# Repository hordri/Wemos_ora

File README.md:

# Wemos_ora
Nixie clock with Wemos d1 mini and integrated switchmode supply

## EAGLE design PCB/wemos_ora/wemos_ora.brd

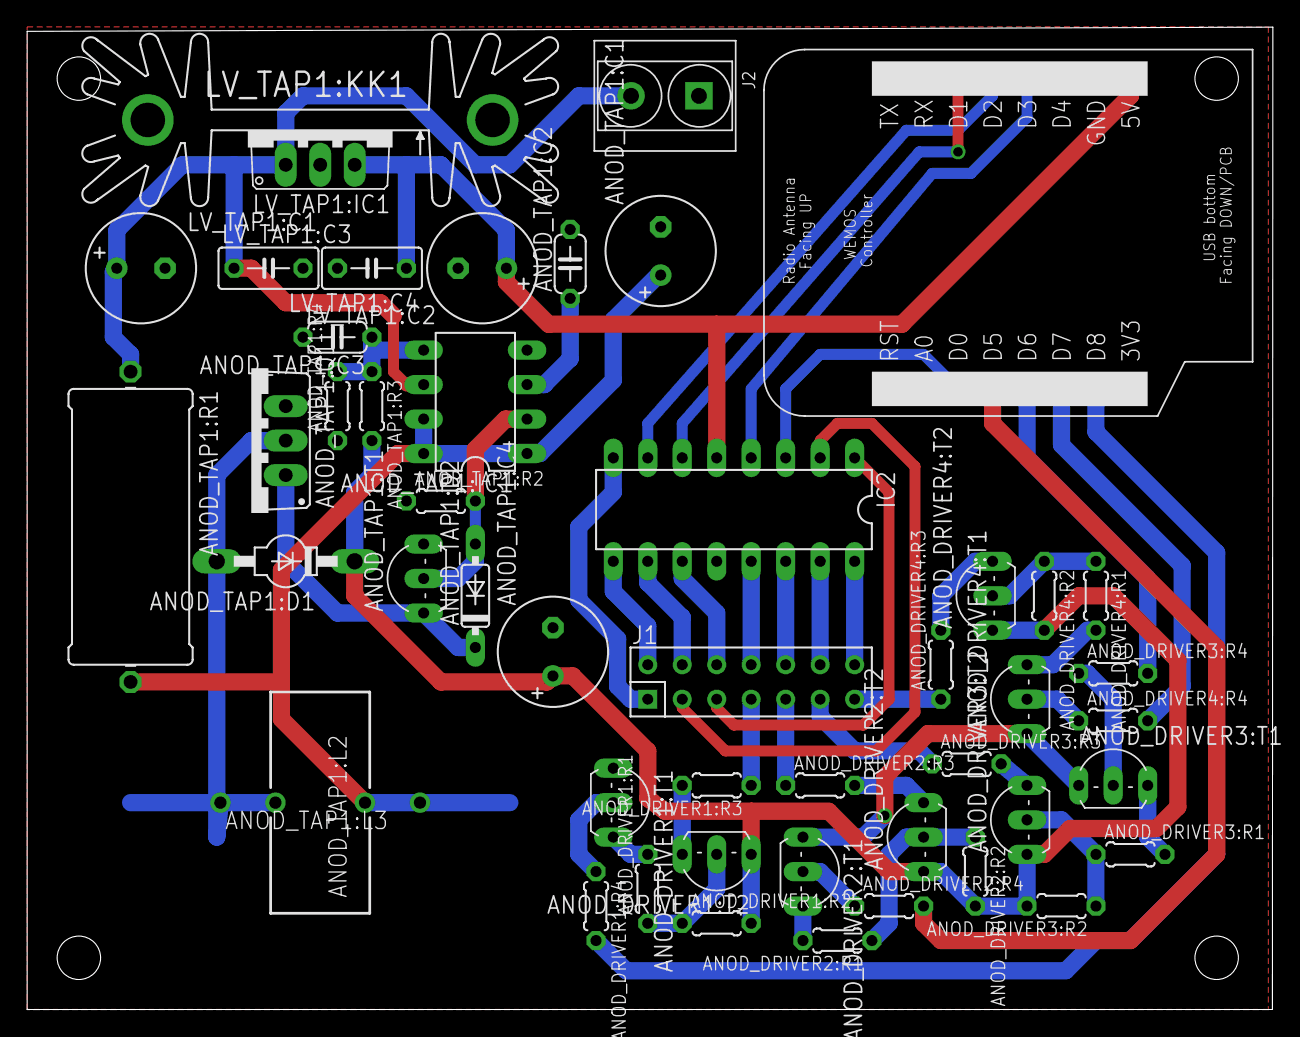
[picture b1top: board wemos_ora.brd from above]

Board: 2 copper layers, 91.8 x 72.4 mm, 50 parts (1 on the bottom side), 48 nets.

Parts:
ANOD_DRIVER1:R1, ANOD_DRIVER2:R1, ANOD_DRIVER3:R1, ANOD_DRIVER4:R1: 470k; 0204/5
ANOD_DRIVER1:R2, ANOD_DRIVER2:R2, ANOD_DRIVER3:R2, ANOD_DRIVER4:R2: 100k; 0204/5
ANOD_DRIVER1:R3, ANOD_DRIVER2:R3, ANOD_DRIVER3:R3, ANOD_DRIVER4:R3: 15k; 0204/5
ANOD_DRIVER1:R4, ANOD_DRIVER2:R4, ANOD_DRIVER3:R4, ANOD_DRIVER4:R4: 22k; 0204/5
ANOD_DRIVER1:T1, ANOD_DRIVER2:T1, ANOD_DRIVER3:T1, ANOD_DRIVER4:T1: MPSA42; TO92-EBC
ANOD_DRIVER1:T2, ANOD_DRIVER2:T2, ANOD_DRIVER3:T2, ANOD_DRIVER4:T2: MPSA92; TO92-EBC
ANOD_TAP1:C1: 220u; E3,5-8
ANOD_TAP1:C2: 2n2; C050-024X044
ANOD_TAP1:C3: 10n; C050-024X044
ANOD_TAP1:C4: 2u2; E3,5-8
ANOD_TAP1:D1: BYV27; SOD57-10
ANOD_TAP1:D2: 1N4148DO35-7; DO35-7
ANOD_TAP1:IC1: MC34063AP; DIL08
ANOD_TAP1:L1: PM2120
ANOD_TAP1:L2: TJ3-U1
ANOD_TAP1:L3: TJ3-U2
ANOD_TAP1:Q1: IRF740; TO220BV
ANOD_TAP1:R1: 0R47; 0922/22
ANOD_TAP1:R2: 1k; 0204/5
ANOD_TAP1:R3: 470k; 0204/5
ANOD_TAP1:R4: 3k3; 0204/5
ANOD_TAP1:T1: MPSA92; TO92-EBC
IC2: 74141N; DIL16
J1: CON_HEADER_2X07-PTH; M2X7
J2: 2p-5.08; H2-5.0-10.5X8.0MM
LV_TAP1:C1, LV_TAP1:C2: 470u; E3,5-8
LV_TAP1:C3, LV_TAP1:C4: 100n; C050-030X075
LV_TAP1:IC1: 7805TV; TO220V
LV_TAP1:KK1: SK104-PAD
U$1: WEMOS

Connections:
+5V: IC2.5, LV_TAP1:C2.+, LV_TAP1:C4.1, LV_TAP1:IC1.3, U$1.5V
+9V: ANOD_TAP1:IC1.6, ANOD_TAP1:R1.1, J2.2, LV_TAP1:C1.+, LV_TAP1:C3.1, LV_TAP1:IC1.1
+24V: ANOD_DRIVER1:R2.2, ANOD_DRIVER1:T2.E, ANOD_DRIVER2:R2.2, ANOD_DRIVER2:T2.E, ANOD_DRIVER3:R2.2, ANOD_DRIVER3:T2.E, ANOD_DRIVER4:R2.2, ANOD_DRIVER4:T2.E, ANOD_TAP1:C4.+, ANOD_TAP1:D1.C, ANOD_TAP1:R3.2
ANOD_DRIVER1:N$1: ANOD_DRIVER1:R3.2, ANOD_DRIVER1:T2.C
ANOD_DRIVER1:N$2: ANOD_DRIVER1:R1.1, ANOD_DRIVER1:R2.1, ANOD_DRIVER1:T2.B
ANOD_DRIVER1:N$3: ANOD_DRIVER1:R1.2, ANOD_DRIVER1:T1.C
ANOD_DRIVER1:N$4: ANOD_DRIVER1:R4.1, ANOD_DRIVER1:T1.B
ANOD_DRIVER2:N$1: ANOD_DRIVER2:R3.2, ANOD_DRIVER2:T2.C
ANOD_DRIVER2:N$2: ANOD_DRIVER2:R1.1, ANOD_DRIVER2:R2.1, ANOD_DRIVER2:T2.B
ANOD_DRIVER2:N$3: ANOD_DRIVER2:R1.2, ANOD_DRIVER2:T1.C
ANOD_DRIVER2:N$4: ANOD_DRIVER2:R4.1, ANOD_DRIVER2:T1.B
ANOD_DRIVER3:N$1: ANOD_DRIVER3:R3.2, ANOD_DRIVER3:T2.C
ANOD_DRIVER3:N$2: ANOD_DRIVER3:R1.1, ANOD_DRIVER3:R2.1, ANOD_DRIVER3:T2.B
ANOD_DRIVER3:N$3: ANOD_DRIVER3:R1.2, ANOD_DRIVER3:T1.C
ANOD_DRIVER3:N$4: ANOD_DRIVER3:R4.1, ANOD_DRIVER3:T1.B
ANOD_DRIVER4:N$1: ANOD_DRIVER4:R3.2, ANOD_DRIVER4:T2.C
ANOD_DRIVER4:N$2: ANOD_DRIVER4:R1.1, ANOD_DRIVER4:R2.1, ANOD_DRIVER4:T2.B
ANOD_DRIVER4:N$3: ANOD_DRIVER4:R1.2, ANOD_DRIVER4:T1.C
ANOD_DRIVER4:N$4: ANOD_DRIVER4:R4.1, ANOD_DRIVER4:T1.B
ANOD_TAP1:N$1: ANOD_TAP1:C1.+, ANOD_TAP1:IC1.1, ANOD_TAP1:IC1.7, ANOD_TAP1:IC1.8, ANOD_TAP1:L1.1, ANOD_TAP1:L2.1, ANOD_TAP1:L3.1, ANOD_TAP1:R1.2
ANOD_TAP1:N$3: ANOD_TAP1:D1.A, ANOD_TAP1:L1.2, ANOD_TAP1:L2.2, ANOD_TAP1:L3.2, ANOD_TAP1:Q1.D
ANOD_TAP1:N$4: ANOD_TAP1:D2.A, ANOD_TAP1:IC1.2, ANOD_TAP1:R2.2, ANOD_TAP1:T1.B
ANOD_TAP1:N$5: ANOD_TAP1:D2.C, ANOD_TAP1:Q1.G, ANOD_TAP1:T1.E
ANOD_TAP1:N$8: ANOD_TAP1:C2.1, ANOD_TAP1:IC1.3
ANOD_TAP1:N$14: ANOD_TAP1:C3.1, ANOD_TAP1:IC1.5, ANOD_TAP1:R3.1, ANOD_TAP1:R4.2
GND: ANOD_DRIVER1:T1.E, ANOD_DRIVER2:T1.E, ANOD_DRIVER3:T1.E, ANOD_DRIVER4:T1.E, ANOD_TAP1:C1.-, ANOD_TAP1:C2.2, ANOD_TAP1:C3.2, ANOD_TAP1:C4.-, ANOD_TAP1:IC1.4, ANOD_TAP1:Q1.S, ANOD_TAP1:R2.1, ANOD_TAP1:R4.1, ANOD_TAP1:T1.C, IC2.12, J2.1, LV_TAP1:C1.-, LV_TAP1:C2.-, LV_TAP1:C3.2, LV_TAP1:C4.2, LV_TAP1:IC1.2, U$1.GND
unnamed: IC2.16, J1.14
unnamed: IC2.15, J1.12
unnamed: IC2.8, J1.1
unnamed: IC2.9, J1.2
unnamed: IC2.13, J1.8
unnamed: IC2.14, J1.10
unnamed: IC2.11, J1.6
unnamed: IC2.10, J1.4
unnamed: IC2.1, J1.5
unnamed: IC2.2, J1.3
unnamed: ANOD_DRIVER1:R3.1, J1.7
unnamed: ANOD_DRIVER2:R3.1, J1.9
unnamed: ANOD_DRIVER3:R3.1, J1.11
unnamed: ANOD_DRIVER4:R3.1, J1.13
unnamed: IC2.3, U$1.D0
unnamed: IC2.6, U$1.D1
unnamed: IC2.7, U$1.D2
unnamed: IC2.4, U$1.D3
unnamed: ANOD_DRIVER1:R4.2, U$1.D8
unnamed: ANOD_DRIVER2:R4.2, U$1.D5
unnamed: ANOD_DRIVER3:R4.2, U$1.D6
unnamed: ANOD_DRIVER4:R4.2, U$1.D7

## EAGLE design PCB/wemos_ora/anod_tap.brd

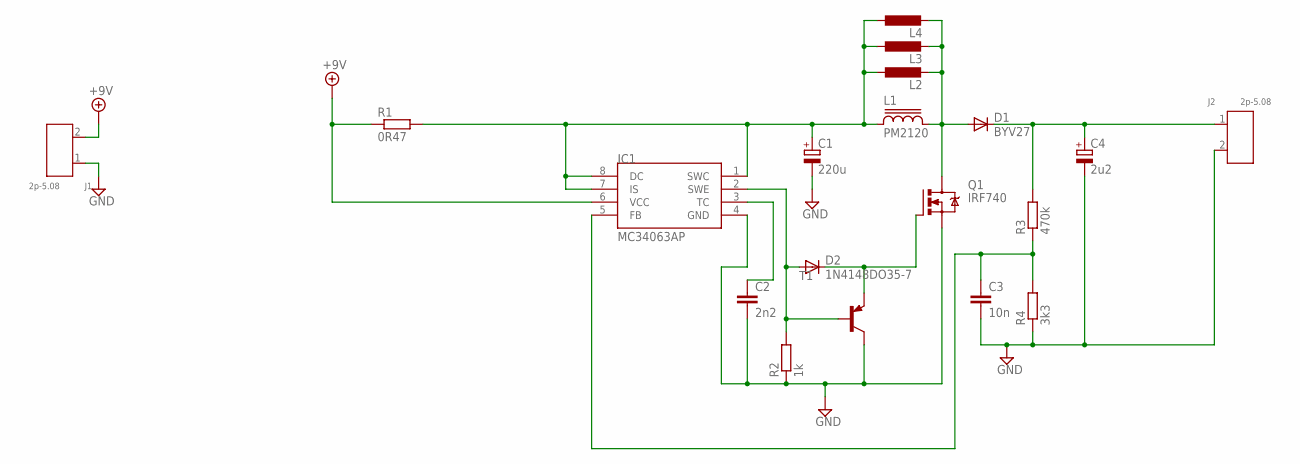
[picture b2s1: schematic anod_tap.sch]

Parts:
C1: 220u; E3,5-8
C2: 2n2; C050-024X044
C3: 10n; C050-024X044
C4: 2u2; E3,5-8
D1: BYV27; SOD57-10
D2: 1N4148DO35-7; DO35-7
IC1: MC34063AP; DIL08
J1, J2: 2p-5.08; H2-5.0-10.5X8.0MM
L1: PM2120
L2: L-EUTJ3-U1; TJ3-U1
L3: L-EUTJ3-U2; TJ3-U2
L4: L-EUTJ4-U2; TJ4-U2
Q1: IRF740; TO220BV
R1: 0R47; 0922/22
R2: 1k; 0204/5
R3: 470k; 0204/5
R4: 3k3; 0204/5
T1: MPSA92-PNP-TO92-EBC; TO92-EBC

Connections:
+9V: IC1.6 (VCC), J1.2, R1.1
GND: C1.-, C2.2, C3.2, C4.-, IC1.4 (GND), J1.1, J2.2, Q1.S, R2.1, R4.1, T1.C
unnamed: C1.+, IC1.1 (SWC), IC1.7 (IS), IC1.8 (DC), L1.1, L2.1, L3.1, L4.1, R1.2
unnamed: D2.A, IC1.2 (SWE), R2.2, T1.B
unnamed: D2.C, Q1.G, T1.E
unnamed: D1.A, L1.2, L2.2, L3.2, L4.2, Q1.D
unnamed: C2.1, IC1.3 (TC)
unnamed: C4.+, D1.C, J2.1, R3.2
unnamed: C3.1, IC1.5 (FB), R3.1, R4.2

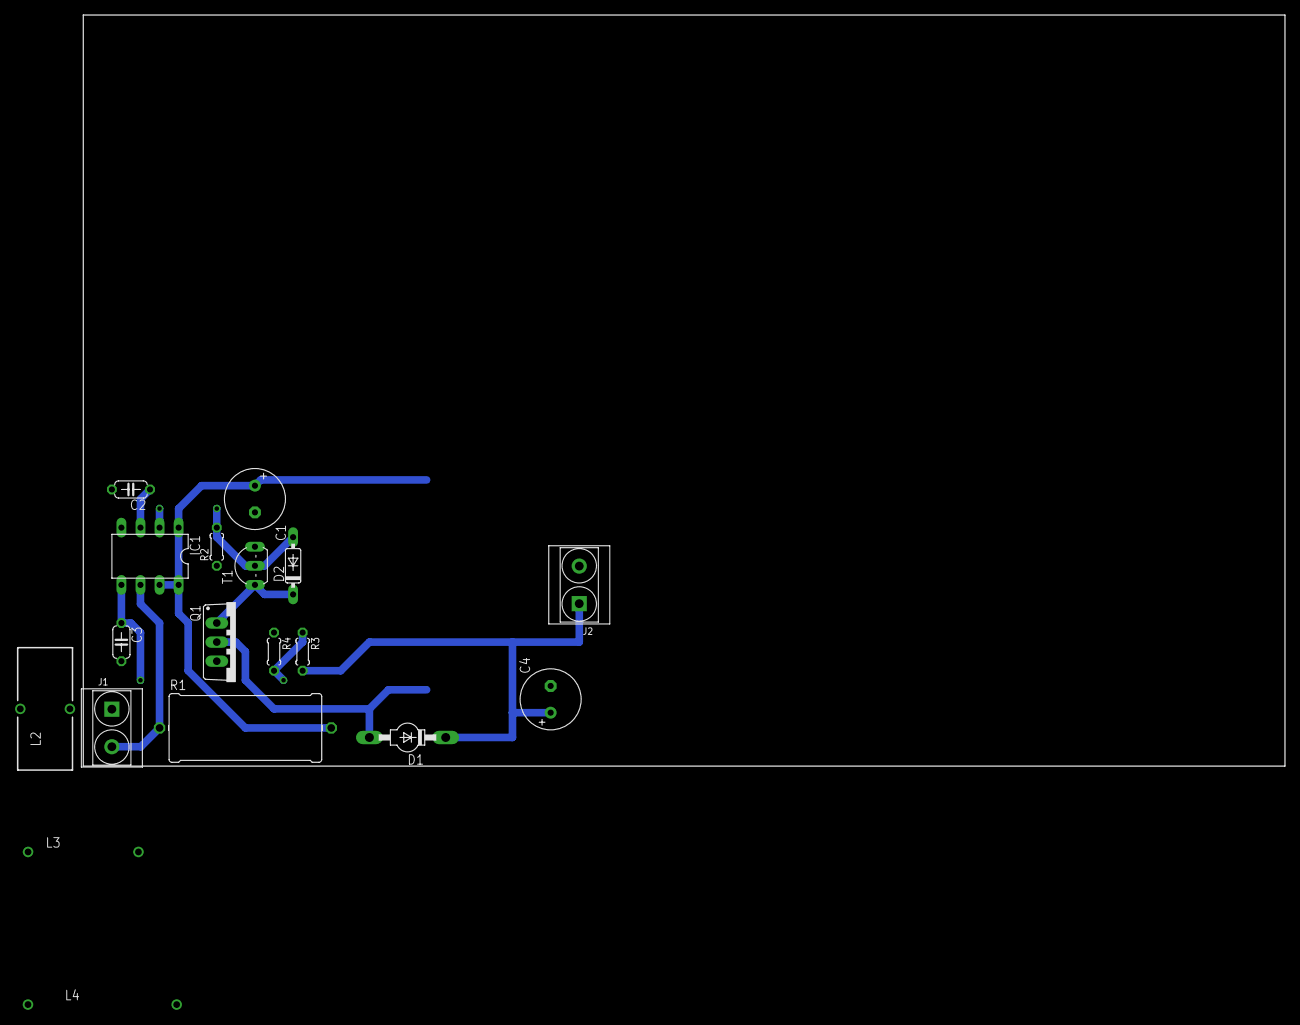
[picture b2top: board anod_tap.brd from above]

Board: 2 copper layers, 160.0 x 100.0 mm, 19 parts (1 on the bottom side), 9 nets.

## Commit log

2019-11-18 Cleaned up version with WifiManager added
2019-11-18 Pinout of the doublerow connector
2019-11-18 Create LICENSE
2019-11-27 firmware for 6 tubes with blinking built in LED
2019-12-12 Materials needed for the PCB
2019-12-12 Parts needed

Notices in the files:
parts and their libraries:
inductor-bourns: Copyright (C) 2008, Bob Starr
